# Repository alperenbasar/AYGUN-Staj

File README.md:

Projeler

---

## Kullanılan Donanım ve Araçlar
- **Mikrodenetleyiciler & Geliştirme Kartları:** STM32F429I-DISC1 (ARM Cortex-M4 @ 180 MHz), Microchip PIC12F1822, Arduino (AVR)
- **Devre Tasarımı & Prototipleme (EDA):** Altium Designer (v26), KiCad, LPKF S63 PCB Kazıma Makinesi (CNC Prototipleme), SMD/THT Dizgi ve Lehimleme
- **Yazılım & Geliştirme Ortamları:** C/C++, Python (Tkinter, pySerial), STM32CubeIDE (HAL Kütüphaneleri, FatFs), MPLAB X IDE (XC8 Derleyici), PICkit 3, Tera Term
- **Sensörler & Aktüatörler:** MPU6050 (İvmeölçer ve Jiroskop), INA226 (Hassas Güç Analizörü), LDR Sensörler, FT5325M Servo Motorlar
- **Haberleşme, Güç & Arayüz Modülleri:** HC-08 Bluetooth Low Energy (BLE), MicroSD Kart Modülü (SPI), CN3303 Lityum Batarya Şarj Kontrolcüsü, 2.4" QVGA TFT LCD (LTDC), STMPE811 Dokunmatik Kontrolcü

---

## Proje İndeksi

1. [01-MPPT-Solar-Tracker(Bitirme_Projesi)](./01-MPPT-Solar-Tracker(Bitirme_Projesi))
   - LDR sensörler ve FT5325M servo motorlar kullanılarak güneş panellerinin ışık kaynağına göre maksimum verimle yönelimini sağlayan Arduino tabanlı çift eksenli elektromekanik sistem tasarımı.
   - INA226 hassas güç sensörleri ile anlık akım ve gerilim verilerinin işlenmesi, yazılımsal MPPT (Maksimum Güç Noktası Takibi) analizi ve sistem verimlilik optimizasyonunun gerçekleştirilmesi.
   - Gömülü sistem yazılımı, motor kontrol mantığı ve donanım entegrasyonu süreçlerinin uçtan uca tamamlanması.

2. [02-PIC12F1822-Sarj-Gostergesi-PCB-Kart-Tasarimi-ve-Basimi](./02-PIC12F1822-Sarj-Gostergesi-PCB-Kart-Tasarimi-ve-Basimi)
   - CN3303 lityum şarj entegresi ile tam uyumlu çalışan, Microchip PIC12F1822 (SOIC-8) kullanılarak tasarlanmış akıllı şarj durum göstergesi ve 3 kademeli (Kırmızı-Sarı-Yeşil) kümülatif dolum animasyonu kontrol kartı.
   - KiCad ile şematik tasarımı ve LPKF S63 kazıma tezgahına uygun tek katmanlı PCB yerleşimi. Şarj modülünün open-drain çıkışında oluşan kaçak akımları ve LED çakışmalarını önlemek amacıyla yüksek empedanslı gerilim bölücü (22K/100K) kullanılarak donanımsal izolasyon sağlandı.
   - STAT pininden gelen kararsız voltaj seviyeleri dijital GPIO yerine ADC ile okundu. Şarj entegresinin mod geçişlerinde yarattığı sinyal gürültülerini ve LED dalgalanmalarını sıfıra indirmek için yazılımsal gerilim eşiği ve 1 saniyelik zaman tabanlı stabilizasyon (debounce) algoritmaları geliştirildi.

3. [03-Akilli-PC-Kilit-Sistemi](./03-Akilli-PC-Kilit-Sistemi)
   - STM32F429I dokunmatik ekranı üzerinden çalışan gömülü şifre doğrulama sistemi.
   - Python tabanlı tam ekran kalkanı (overlay) ile bilgisayar erişimini engelleme/açma.
   - HC-08 BLE modülü üzerinden mobil cihaza anlık durum telemetrisi iletimi.

4. [04-STM32-MPU6050-ile-Akilli-Guvenlik-Sistemi](./04-STM32-MPU6050-ile-Akilli-Guvenlik-Sistemi)
   - MPU6050 ivmeölçer/jiroskop sensörü ile hassas anomali (hareket/sarsıntı) tespiti yapan çok katmanlı alarm sistemi.
   - İhlal durumunda PC'ye seri port üzerinden uyarı iletimi ve Notify API ile akıllı telefona mobil "Push" bildirim entegrasyonu.
   - Dahili dokunmatik TFT ekranın Numpad arayüzü olarak kullanılarak alarmın donanımsal şifre ile iptal edilmesi (Disarm) mekanizması.

5. [05-STM32-GMeter-ve-Karakutu-Veri-Kaydedici](./05-STM32-GMeter-ve-Karakutu-Veri-Kaydedici)
   - MPU6050 ivme verilerinin Low-Pass Filter (Düşük Geçiren Filtre) ile işlenerek ekranda 25 FPS hızında gerçek zamanlı "G-Meter" (Radar) arayüzüne dönüştürülmesi.
   - Araç dinamiği verilerinin (Zaman, AccX, AccY, AccZ) MicroSD karta (FAT32) donanımsal SPI hattı üzerinden kesintisiz bir `.csv` dosyası olarak kaydedilmesi (Data Logging).
   - Ekranın LTDC/SDRAM DMA veri trafiği ile SD kartın SPI okuma/yazma döngüleri arasındaki veri yolu çakışmalarının (Bus matrix congestion), donanımsal pin izolasyonu (CS pini tahsisi) ile kilitlenmeden (non-blocking) çözümlenmesi.

6. [06-BLE-Tetiklemeli ve PC-Kontrollu-Hibrit-LED-Otomasyon-Sistemi](./06-BLE-Tetiklemeli%20ve%20PC-Kontrollu-Hibrit-LED-Otomasyon-Sistemi)
   - Telefondan gelen Bluetooth komutuyla tetiklenen durum makinesi (state machine) mimarisi.
   - PC terminaline dinamik menü basılması ve klavye girdisine göre dahili/harici LED kontrolü.
   - Seri port kilitlenmelerini önleyen `ORE` (Overrun Error) hata yönetimi.

7. [07-STM32F429--Dahili-TFT-LCD ile 3D-Starfield-Grafik-Simülasyonu](./07-STM32F429--Dahili-TFT-LCD%20ile%203D-Starfield-Grafik-Simülasyonu)
   - 3 boyutlu uzay koordinatlarının ($X, Y, Z$) ekrana 2D perspektif izdüşümü ile yansıtılması.
   - Harici SDRAM üzerinde ekran yırtılmasını (flicker) engelleyen dinamik piksel temizleme ve çizim tekniğiyle 70 parçacıklı yıldız alanı simülasyonu.

8. [08-STM32F429I-DISC1-Dahili-TFT-LCD-Ekran-İlk-Surus-Denemesi (BSP Hello World)](./08-STM32F429I-DISC1-Dahili-TFT-LCD-Ekran-İlk-Surus-Denemesi%20(BSP%20Hello%20World))
   - Dahili 2.4" TFT LCD ekranın BSP sürücü katmanı ile ayağa kaldırılması ("Hello World" testi).
   - Maksimum çekirdek frekansı (180 MHz Over-Drive) ve temel saat/güç konfigürasyonunun doğrulanması.

9. [09-STM32-Donanimsal-Timer-PWM ile Puruzsuz-LED-Parlaklik-Kontrolu](./09-STM32-Donanimsal-Timer-PWM%20ile%20Puruzsuz-LED-Parlaklik-Kontrolu)
   - `TIM1 Channel 1` üzerinden donanımsal Darbe Genişlik Modülasyonu (PWM) sinyali üretimi.
   - 1000 adımlı yüksek çözünürlükle akıcı ve titreşimsiz "Breathing / Nefes Alma" görsel efekti.

10. [10-Telefon-PC-Haberlesme-Koprusu](./10-Telefon-PC-Haberlesme-Koprusu)
    - Akıllı telefon (BLE Terminal) ile bilgisayar (Tera Term) arasında iki yönlü seri haberleşme köprüsü.
    - Asenkron veri alımı için kesme tabanlı altyapı (`HAL_UART_Receive_IT`) ve callback yönetimi.

11. [11-STM32-12-Bit-ADC-Okumasi ile Gercek-Zamanli-PWM-Parlaklik-Kontrolu](./11-STM32-12-Bit-ADC-Okumasi%20ile%20Gercek-Zamanli-PWM-Parlaklik-Kontrolu)
    - Potansiyometre üzerinden 12-bit çözünürlükte (0–4095) analog gerilim verisi okuma (`ADC1`).
    - Matematiksel ölçekleme ile analog değerin `TIM3` PWM doluluk oranına dönüştürülmesi ve gerçek zamanlı LED parlaklık ayarı.

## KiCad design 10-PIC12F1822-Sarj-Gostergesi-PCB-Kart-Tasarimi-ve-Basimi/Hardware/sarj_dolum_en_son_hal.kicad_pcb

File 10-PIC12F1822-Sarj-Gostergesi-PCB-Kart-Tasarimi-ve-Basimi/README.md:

# 10-PIC12F1822-Sarj-Gostergesi-PCB-Kart-Tasarimi-ve-Basimi

Bu repo, Microchip PIC12F1822 8-bit mikrodenetleyici tabanlı, CN3303 lityum şarj entegresi ile tam uyumlu çalışan özel bir şarj durum göstergesi kontrolcüsü için uçtan uca tasarım, prototipleme, donanımsal sinyal izolasyonu, PCB yerleşimi ve gömülü yazılım süreçlerini içermektedir.

Bu proje, yeni geliştirilen bir donanım ürünü üzerinde görsel bir kümülatif şarj animasyonu (Kırmızı-Sarı-Yeşil) ve dolum durum göstergesi sağlanması yönündeki mühendislik talebini karşılamak amacıyla hayata geçirilmiştir.

---

## Geliştirme Aşamaları ve Donanımsal Çözümler

1. Gereksinimler ve Şematik Tasarım: Giriş sinyalleri (`STAT` şarj sinyali) ve çıkış gereksinimleri belirlendi. KiCad üzerinden şematik çizimi tamamlandı.
2. Sinyal İzolasyonu ve Prototipleme: İlk prototiplemede şarj modülünün (CN3303) open-drain çıkışında mikrodenetleyicinin dijital giriş ve pull-up dirençlerinden kaynaklı kaçak akımlar ve LED çakışmaları tespit edildi. Bu donanımsal kilitlenmeyi çözmek amacıyla, giriş hattında yüksek empedanslı bir gerilim bölücü (22K seri, 100K pull-down) kullanılarak tam elektriksel izolasyon sağlandı.
3. PCB Yerleşimi ve Üretim: Şirket içi prototipleme süreçlerine (LPKF kazıma/frezeleme yöntemi) uygun, kompakt ve tek yüzlü bir PCB tasarımı yapıldı. Testler sonrası, laboratuvar tipi manuel lehimleme ile donanım ayağa kaldırıldı.
4. Gömülü Yazılım ve ADC Filtreleme: Sinyal gürültülerini (CN3303'ün pil arama modundaki voltaj dalgalanmalarını) sıfıra indirmek için, `STAT` pini dijital GPIO yerine ADC (Analog-Dijital Çevirici) ile okundu. MPLAB X IDE ve XC8 derleyicisi kullanılarak; yazılımsal histerezis (gerilim eşiği), 1 saniyelik zaman tabanlı stabilizasyon (debounce) algoritmaları ve State Machine mimarisi C dilinde kodlandı.

---

## Donanım Özellikleri

*   Mikrodenetleyici: Microchip PIC12F1822 (SOIC-8)
*   Osilatör: Dahili 4 MHz HFINTOSC (Harici kristal osilatöre ihtiyaç duyulmaz)
*   Giriş Arayüzü (Analog): CN3303'ün `STAT` hattından gelen sinyal, kaçak akımları önlemek için 22K (R4) seri direnç ve 100K (R5) pull-down direnci üzerinden RA0 pinine bağlanmıştır.
*   Çıkış Arayüzü: `RA5`, `RA4` ve `RA2` pinleri üzerinden 470 Ω dirençlerle sürülen 3 kademeli (Kırmızı, Sarı, Yeşil) durum LED'leri.
*   Programlama Arayüzü: PICkit 3 ile doğrudan kart üzerinden hata ayıklama (debug) ve kod yükleme imkanı sunan yerleşik ICSP (In-Circuit Serial Programming) başlığı. *(Not: RA3/MCLR pini donanımsal izolasyon sebebiyle yazılım okumasından çıkarılmıştır).*

---

## Repo Klasör Yapısı

*   `Firmware/`: MPLAB X C kaynak kodlarını (`main.c`) ve üretim hex dosyalarını barındırır.
*   `Hardware/`: KiCad şematik (`.kicad_sch`) ve PCB yerleşim (`.kicad_pcb`) dosyalarını içerir.
*   `Images/`: Breadboard testlerini, kazınan PCB'yi, donanımsal modifikasyonları ve final montajı belgeleyen fotoğrafları barındırır.

---

## Yazılım (Firmware) Genel Bakış

Yazılım; donanımsal gürültüleri ve kararsız mod geçişlerini (örn. pil bağlı değilken oluşan osilasyonları) engellemek için sinyali Analog (ADC) olarak okur. Belirlenen histerezis eşikleri (`ADC_CHARGE_MIN` ve `ADC_FULL_MAX`) ve 1 saniyelik zaman bazlı filtreleme ile temizlenmiş sinyal üzerinden şarj kümülatif animasyonunu yönetir. Durum makinesi mantığı sayesinde işlemci animasyon sırasında kör (kilitli) kalmaz.

10-PIC12F1822-Sarj-Gostergesi-PCB-Kart-Tasarimi-ve-Basimi/Software/main.c

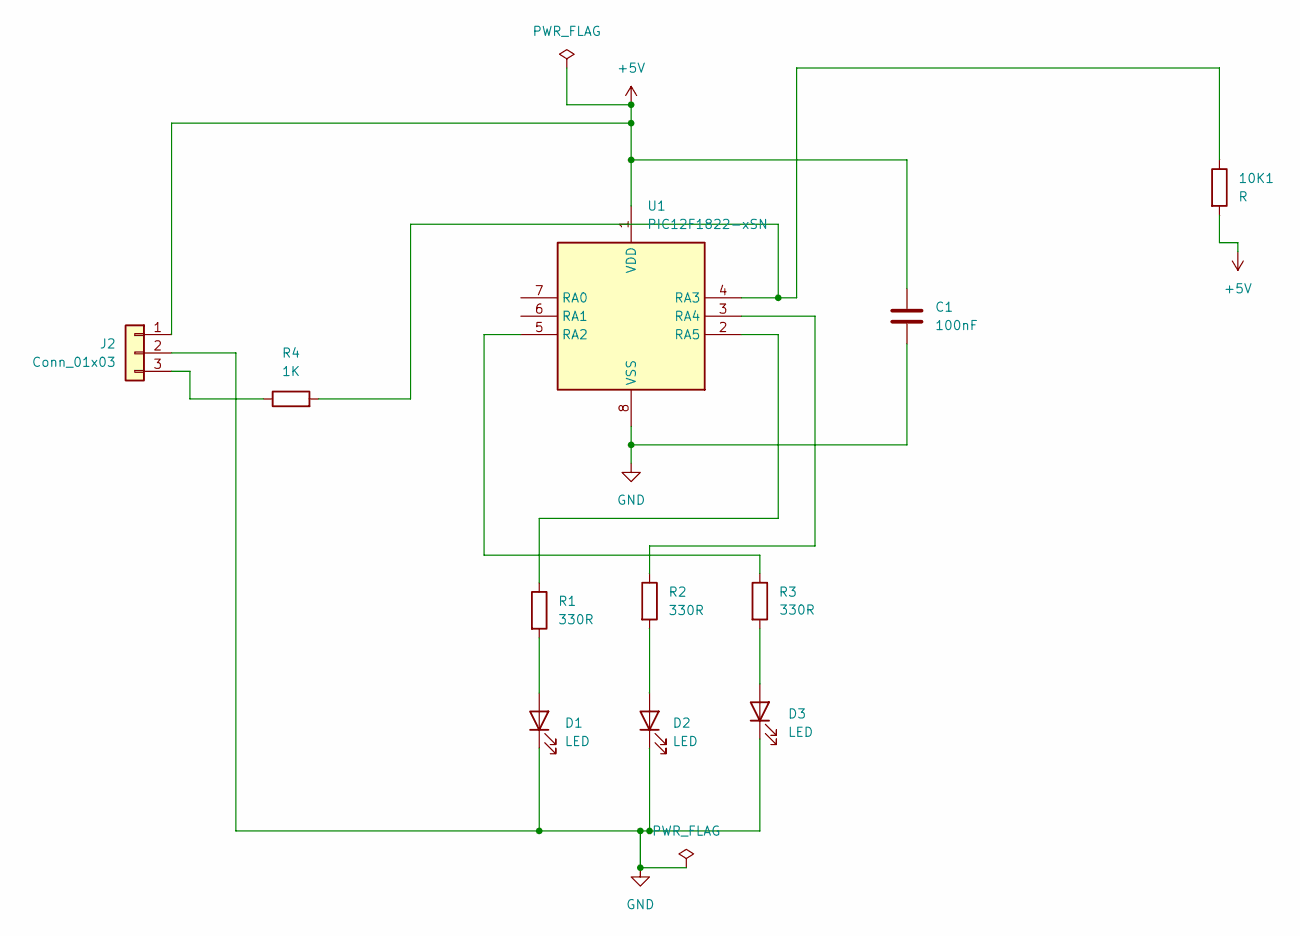
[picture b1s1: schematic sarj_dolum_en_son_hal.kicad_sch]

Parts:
10K1: R; R_Axial_DIN0207_L6.3mm_D2.5mm_P10.16mm_Horizontal
C1: 100nF; C_Disc_D5.0mm_W2.5mm_P5.00mm
D1, D2, D3: LED; LED_D3.0mm
J2: Conn_01x03; PinHeader_1x03_P2.54mm_Vertical
R1, R2, R3: 330R; R_Axial_DIN0207_L6.3mm_D2.5mm_P10.16mm_Horizontal
R4: 1K; R_Axial_DIN0207_L6.3mm_D2.5mm_P10.16mm_Horizontal
U1: PIC12F1822-xSN; SOIC-8_3.9x4.9mm_P1.27mm

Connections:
+5V: 10K1.2, C1.1, J2.1, U1.1 (VDD)
GND: C1.2, D1.1 (K), D2.1 (K), D3.1 (K), J2.2, U1.8 (VSS)
unnamed: D1.2 (A), R1.2
unnamed: D2.2 (A), R2.2
unnamed: D3.2 (A), R3.2
unnamed: J2.3, R4.1
unnamed: R3.1, U1.5 (RA2)
unnamed: 10K1.1, R4.2, U1.4 (RA3)
unnamed: R2.1, U1.3 (RA4)
unnamed: R1.1, U1.2 (RA5)

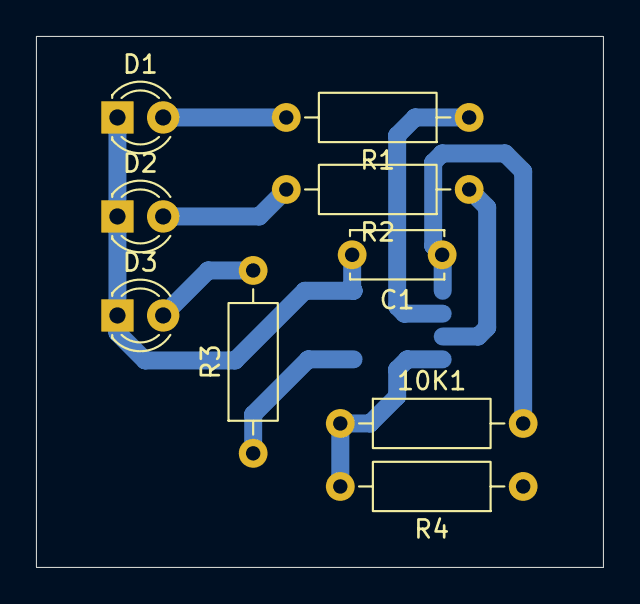
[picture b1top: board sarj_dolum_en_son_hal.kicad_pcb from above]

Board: 2 copper layers, 31.5 x 29.5 mm, 10 parts (1 on the bottom side), 9 nets.
